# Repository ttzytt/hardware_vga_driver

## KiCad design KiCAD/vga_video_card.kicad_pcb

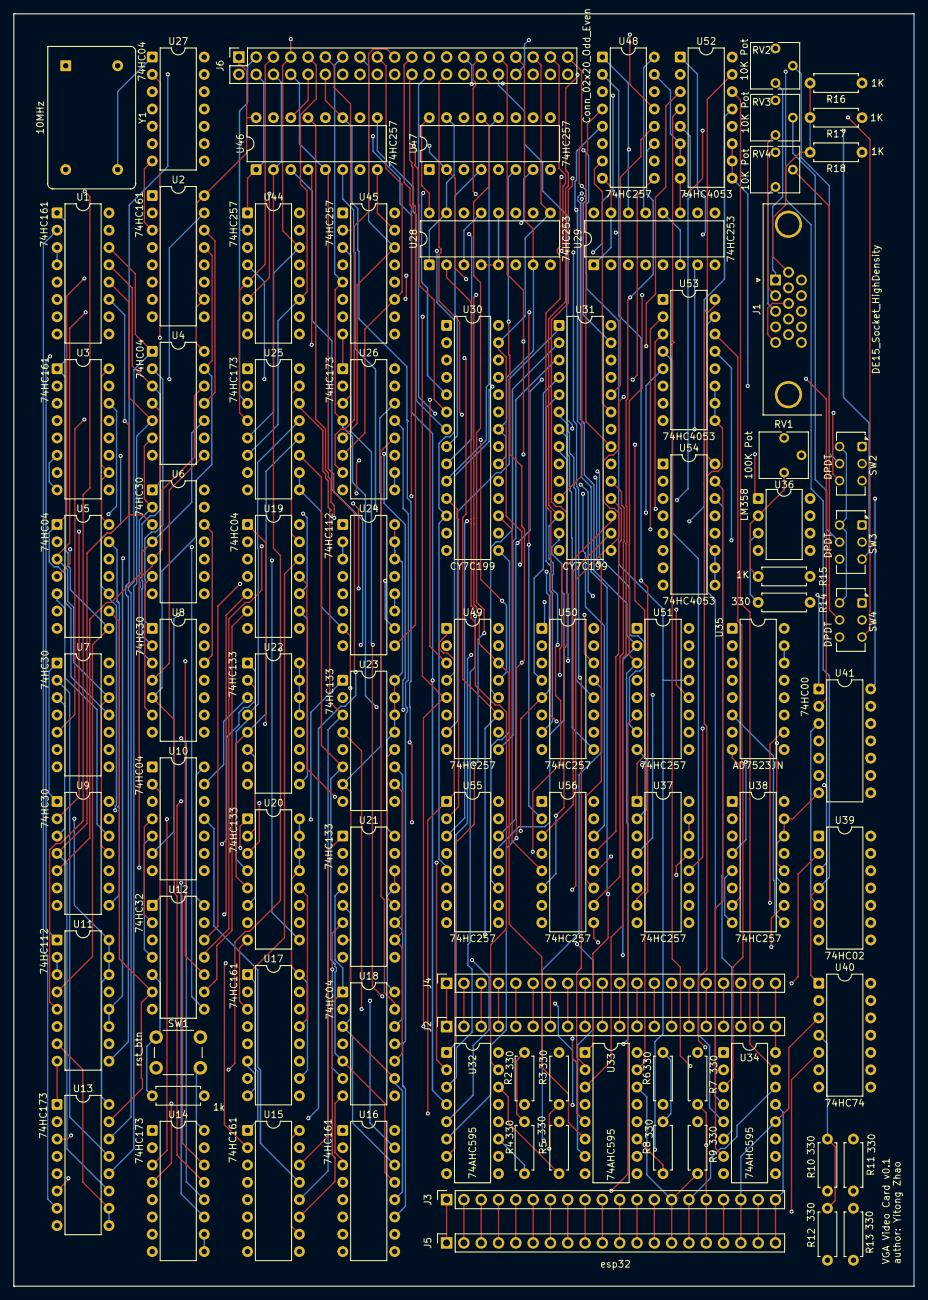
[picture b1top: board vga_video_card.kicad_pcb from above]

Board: 4 copper layers, 132.1 x 186.7 mm, 87 parts (0 on the bottom side), 231 nets.

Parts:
J1: DE15_Socket_HighDensity; DSUB-15-HD_Socket_Horizontal_P2.29x1.90mm_EdgePinOffset3.03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
J2, J3, J4, J5: Conn_01x20; PinSocket_1x20_P2.54mm_Vertical
J6: Conn_02x20_Odd_Even; PinSocket_2x20_P2.54mm_Vertical
R1: 1k; R_Axial_DIN0207_L6.3mm_D2.5mm_P7.62mm_Horizontal
R2, R3, R4, R5, R6, R7, R8, R9, R10, R11, R12, R13, R14: 330; R_Axial_DIN0207_L6.3mm_D2.5mm_P7.62mm_Horizontal
R15, R16, R17, R18: 1K; R_Axial_DIN0207_L6.3mm_D2.5mm_P7.62mm_Horizontal
RV1: 100K Pot; Potentiometer_Vishay_T73YP_Vertical
RV2, RV3, RV4: 10K Pot; Potentiometer_Vishay_T73YP_Vertical
SW1: rst_btn; SW_PUSH_6mm
SW2, SW3, SW4: DPDT; SW_CK_JS202011CQN_DPDT_Straight
U1, U2, U3, U15, U16, U17: 74HC161; DIP-16_W7.62mm
U4, U5, U10, U18, U19, U27: 74HC04; DIP-14_W7.62mm
U6, U7, U8, U9: 74HC30; DIP-14_W7.62mm
U11, U24: 74HC112; DIP-16_W7.62mm
U12: 74HC32; DIP-14_W7.62mm
U13, U14, U25, U26: 74HC173; DIP-16_W7.62mm
U20, U21, U22, U23: 74HC133; DIP-16_W7.62mm
U28, U29: 74HC253; DIP-16_W7.62mm
U30, U31: CY7C199; DIP-28_W7.62mm
U32, U33, U34: 74AHC595; DIP-16_W7.62mm
U35: AD7523JN; DIP-16_W7.62mm
U36: LM358; DIP-8_W7.62mm
U37, U38, U44, U45, U46, U47, U48, U49, U50, U51, U55, U56: 74HC257; DIP-16_W7.62mm
U39: 74HC02; DIP-14_W7.62mm
U40: 74HC74; DIP-14_W7.62mm
U41: 74HC00; DIP-14_W7.62mm
U52, U53, U54: 74HC4053; DIP-16_W7.62mm
Y1: 10MHz; Oscillator_DIP-14

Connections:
+5V: J2.20, J4.20, J6.1, R2.2, R3.2, R4.2, R5.2, R6.2, R7.2, R8.2, R9.2, R10.2, R11.2, R12.2, R13.2, SW1.2, U1.7 (CEP), U1.10 (CET), U1.16 (VCC), U2.7 (CEP), U2.10 (CET), U2.16 (VCC), U3.7 (CEP), U3.10 (CET), U3.16 (VCC), U4.14 (VCC), U5.14 (VCC), U6.14 (VCC), U7.14 (VCC), U8.14 (VCC), U9.14 (VCC), U10.14 (VCC), U11.14 (~R), U11.15 (~R), U11.16 (VCC), U12.14 (VCC), U13.16 (VCC), U14.16 (VCC), U15.7 (CEP), U15.10 (CET), U15.16 (VCC), U16.7 (CEP), U16.10 (CET), U16.16 (VCC), U17.7 (CEP), U17.10 (CET), U17.16 (VCC), U18.14 (VCC), U19.14 (VCC), U20.13, U20.14, U20.15, U20.16 (VCC), U21.13, U21.14, U21.15, U21.16 (VCC), U22.13, U22.14, U22.15, U22.16 (VCC), U23.13, U23.14, U23.15, U23.16 (VCC), U24.14 (~R), U24.15 (~R), U24.16 (VCC), U25.16 (VCC), U26.16 (VCC), U27.14 (VCC), U28.3 (I3a), U28.10 (I0b), U28.11 (I1b), U28.13 (I3b), U28.16 (VCC), U29.6 (I0a), U29.10 (I0b), U29.12 (I2b), U29.13 (I3b), U29.16 (VCC), U30.28 (VCC), U31.28 (VCC), U32.16 (VCC), U33.16 (VCC), U34.16 (VCC), U35.14 (VCC), U35.15 (VREF), U36.8 (V+), U37.16 (VCC), U38.16 (VCC), U39.14 (VCC), U40.2 (D), U40.4 (~S), U40.14 (VCC), U41.14 (VCC), U44.16 (VCC), U45.16 (VCC), U46.16 (VCC), U47.16 (VCC), U48.16 (VCC), U49.16 (VCC), U50.16 (VCC), U51.16 (VCC), U52.16 (VDD), U53.16 (VDD), U54.16 (VDD), U55.16 (VCC), U56.16 (VCC), Y1.1 (EN), Y1.14 (Vcc)
/ADC_module/D0: U35.13 (D0(LSB)), U37.4 (Za)
/ADC_module/D1: U35.12 (D1), U37.7 (Zb)
/ADC_module/D2: U35.11 (D2), U37.12 (Zc)
/ADC_module/D3: U35.10 (D3), U37.9 (Zd)
/ADC_module/D4: U35.9 (D4), U38.4 (Za)
/ADC_module/D5: U35.8 (D5), U38.7 (Zb)
/ADC_module/D6: U35.7 (D6), U38.12 (Zc)
/ADC_module/D7: U35.6 (D7), U38.9 (Zd)
/ADC_module/I0: U37.3 (I1a), U55.4 (Za)
/ADC_module/I1: U37.6 (I1b), U55.7 (Zb)
/ADC_module/I2: U37.13 (I1c), U55.12 (Zc)
/ADC_module/I3: U37.10 (I1d), U55.9 (Zd)
/ADC_module/I4: U38.3 (I1a), U56.4 (Za)
/ADC_module/I5: U38.6 (I1b), U56.7 (Zb)
/ADC_module/I6: U38.13 (I1c), U56.12 (Zc)
/ADC_module/I7: U38.10 (I1d), U56.9 (Zd)
/RAM0_~CE: J6.33, U28.7 (Za), U30.20 (~CE), U30.22 (~OE)
/RAM0_~WE: J6.35, U28.9 (Zb), U30.27 (~WE), U41.1
/RAM1_~CE: J6.37, U29.7 (Za), U31.20 (~CE), U31.22 (~OE)
/RAM1_~WE: J6.39, U29.9 (Zb), U31.27 (~WE), U41.2
/RAM_module/RAM0_a0: U30.21 (A0), U44.4 (Za)
/RAM_module/RAM0_a1: U30.23 (A1), U44.7 (Zb)
/RAM_module/RAM0_a2: U30.24 (A2), U44.12 (Zc)
/RAM_module/RAM0_a3: U30.25 (A3), U44.9 (Zd)
/RAM_module/RAM0_a4: U30.26 (A4), U45.4 (Za)
/RAM_module/RAM0_a5: U30.1 (A5), U45.7 (Zb)
/RAM_module/RAM0_a6: U30.2 (A6), U45.12 (Zc)
/RAM_module/RAM0_a7: U30.3 (A7), U45.9 (Zd)
/RAM_module/RAM0_a8: U30.4 (A8), U46.4 (Za)
/RAM_module/RAM0_a9: U30.5 (A9), U46.7 (Zb)
/RAM_module/RAM0_a10: U30.6 (A10), U46.12 (Zc)
/RAM_module/RAM0_a11: U30.7 (A11), U46.9 (Zd)
/RAM_module/RAM0_a12: U30.8 (A12), U47.4 (Za)
/RAM_module/RAM0_a13: U30.9 (A13), U47.7 (Zb)
/RAM_module/RAM0_a14: U30.10 (A14), U47.12 (Zc)
/RAM_module/RAM0_d0: U30.11 (D0), U52.13 (X1), U55.2 (I0a)
/RAM_module/RAM0_d1: U30.12 (D1), U52.1 (Y1), U55.5 (I0b)
/RAM_module/RAM0_d2: U30.13 (D2), U52.3 (Z1), U55.14 (I0c)
/RAM_module/RAM0_d3: U30.15 (D3), U53.13 (X1), U55.11 (I0d)
/RAM_module/RAM0_d4: U30.16 (D4), U53.1 (Y1), U56.2 (I0a)
/RAM_module/RAM0_d5: U30.17 (D5), U53.3 (Z1), U56.5 (I0b)
/RAM_module/RAM0_d6: U30.18 (D6), U54.13 (X1), U56.14 (I0c)
/RAM_module/RAM0_d7: U30.19 (D7), U54.1 (Y1), U56.11 (I0d)
/RAM_module/RAM1_a0: U31.21 (A0), U48.4 (Za)
/RAM_module/RAM1_a1: U31.23 (A1), U48.7 (Zb)
/RAM_module/RAM1_a2: U31.24 (A2), U48.12 (Zc)
/RAM_module/RAM1_a3: U31.25 (A3), U48.9 (Zd)
/RAM_module/RAM1_a4: U31.26 (A4), U49.4 (Za)
/RAM_module/RAM1_a5: U31.1 (A5), U49.7 (Zb)
/RAM_module/RAM1_a6: U31.2 (A6), U49.12 (Zc)
/RAM_module/RAM1_a7: U31.3 (A7), U49.9 (Zd)
/RAM_module/RAM1_a8: U31.4 (A8), U50.4 (Za)
/RAM_module/RAM1_a9: U31.5 (A9), U50.7 (Zb)
/RAM_module/RAM1_a10: U31.6 (A10), U50.12 (Zc)
/RAM_module/RAM1_a11: U31.7 (A11), U50.9 (Zd)
/RAM_module/RAM1_a12: U31.8 (A12), U51.4 (Za)
/RAM_module/RAM1_a13: U31.9 (A13), U51.7 (Zb)
/RAM_module/RAM1_a14: U31.10 (A14), U51.12 (Zc)
/RAM_module/RAM1_d0: U31.11 (D0), U52.12 (X0), U55.3 (I1a)
/RAM_module/RAM1_d1: U31.12 (D1), U52.2 (Y0), U55.6 (I1b)
/RAM_module/RAM1_d2: U31.13 (D2), U52.5 (Z0), U55.13 (I1c)
/RAM_module/RAM1_d3: U31.15 (D3), U53.12 (X0), U55.10 (I1d)
/RAM_module/RAM1_d4: U31.16 (D4), U53.2 (Y0), U56.3 (I1a)
/RAM_module/RAM1_d5: U31.17 (D5), U53.5 (Z0), U56.6 (I1b)
/RAM_module/RAM1_d6: U31.18 (D6), U54.12 (X0), U56.13 (I1c)
/RAM_module/RAM1_d7: U31.19 (D7), U54.2 (Y0), U56.10 (I1d)
/RAM_module/RAM_bus_mux/w_addr0: U33.15 (QA), U44.3 (I1a), U48.2 (I0a)
/RAM_module/RAM_bus_mux/w_addr1: U33.1 (QB), U44.6 (I1b), U48.5 (I0b)
/RAM_module/RAM_bus_mux/w_addr2: U33.2 (QC), U44.13 (I1c), U48.14 (I0c)
/RAM_module/RAM_bus_mux/w_addr3: U33.3 (QD), U44.10 (I1d), U48.11 (I0d)
/RAM_module/RAM_bus_mux/w_addr4: U33.4 (QE), U45.3 (I1a), U49.2 (I0a)
/RAM_module/RAM_bus_mux/w_addr5: U33.5 (QF), U45.6 (I1b), U49.5 (I0b)
/RAM_module/RAM_bus_mux/w_addr6: U33.6 (QG), U45.13 (I1c), U49.14 (I0c)
/RAM_module/RAM_bus_mux/w_addr7: U33.7 (QH), U45.10 (I1d), U49.11 (I0d)
/RAM_module/RAM_bus_mux/w_addr8: U32.1 (QB), U46.3 (I1a), U50.2 (I0a)
/RAM_module/RAM_bus_mux/w_addr9: U32.2 (QC), U46.6 (I1b), U50.5 (I0b)
/RAM_module/RAM_bus_mux/w_addr10: U32.3 (QD), U46.13 (I1c), U50.14 (I0c)
/RAM_module/RAM_bus_mux/w_addr11: U32.4 (QE), U46.10 (I1d), U50.11 (I0d)
/RAM_module/RAM_bus_mux/w_addr12: U32.5 (QF), U47.3 (I1a), U51.2 (I0a)
/RAM_module/RAM_bus_mux/w_addr13: U32.6 (QG), U47.6 (I1b), U51.5 (I0b)
/RAM_module/RAM_bus_mux/w_addr14: U32.7 (QH), U47.13 (I1c), U51.14 (I0c)
/RAM_module/RAM_bus_mux/w_data0: U34.15 (QA), U52.14 (X)
/RAM_module/RAM_bus_mux/w_data1: U34.1 (QB), U52.15 (Y)
/RAM_module/RAM_bus_mux/w_data2: U34.2 (QC), U52.4 (Z)
/RAM_module/RAM_bus_mux/w_data3: U34.3 (QD), U53.14 (X)
/RAM_module/RAM_bus_mux/w_data4: U34.4 (QE), U53.15 (Y)
/RAM_module/RAM_bus_mux/w_data5: U34.5 (QF), U53.4 (Z)
/RAM_module/RAM_bus_mux/w_data6: U34.6 (QG), U54.14 (X)
/RAM_module/RAM_bus_mux/w_data7: U34.7 (QH), U54.15 (Y)
/RAM_module/RAM_bus_mux/w_j_addr0: U28.2 (A1), U29.2 (A1), U32.15 (QA)
/RAM_module/await_upd: J3.1, J5.1, U40.5 (Q)
/RAM_module/ext_graphics_rclk: J3.18, J5.18, R2.1, R6.1, R10.1, U32.12 (RCLK), U33.12 (RCLK), U34.12 (RCLK), U40.3 (C)
/RAM_module/ext_graphics_source/data_ser: J3.15, J5.15, R13.1, U34.14 (SER)
/RAM_module/ext_graphics_source/data_srclk: J3.17, J5.17, R4.1, R8.1, R12.1, U32.11 (SRCLK), U33.11 (SRCLK), U34.11 (SRCLK)
/RAM_module/ext_graphics_source/data_~srclr: J3.16, J5.16, R3.1, R7.1, R11.1, U32.10 (~SRCLR), U33.10 (~SRCLR), U34.10 (~SRCLR)
/RAM_module/ext_graphics_source/i_addr_ser: J3.14, J5.14, R9.1, U33.14 (SER)
/RAM_module/ext_graphics_source/j_addr_ser: J3.13, J5.13, R5.1, U32.14 (SER)
/RAM_module/r_i_addr0: J6.3, U25.3 (Q0), U44.2 (I0a), U48.3 (I1a)
/RAM_module/r_i_addr1: J6.5, U25.4 (Q1), U44.5 (I0b), U48.6 (I1b)
/RAM_module/r_i_addr2: J6.7, U25.5 (Q2), U44.14 (I0c), U48.13 (I1c)
/RAM_module/r_i_addr3: J6.9, U25.6 (Q3), U44.11 (I0d), U48.10 (I1d)
/RAM_module/r_i_addr4: J6.11, U26.3 (Q0), U45.2 (I0a), U49.3 (I1a)
/RAM_module/r_i_addr5: J6.13, U26.4 (Q1), U45.5 (I0b), U49.6 (I1b)
/RAM_module/r_i_addr6: J6.15, U26.5 (Q2), U45.14 (I0c), U49.13 (I1c)
/RAM_module/r_i_addr7: J6.17, U26.6 (Q3), U45.11 (I0d), U49.10 (I1d)
/RAM_module/r_j_addr0: J6.4, U13.3 (Q0), U28.14 (A0), U29.14 (A0), U44.1 (S), U45.1 (S), U46.1 (S), U47.1 (S), U48.1 (S), U49.1 (S), U50.1 (S), U51.1 (S), U52.9 (C), U52.10 (B), U52.11 (A), U53.9 (C), U53.10 (B), U53.11 (A), U54.9 (C), U54.10 (B), U54.11 (A), U55.1 (S), U56.1 (S)
/RAM_module/r_j_addr1: J6.6, U13.4 (Q1), U46.2 (I0a), U50.3 (I1a)
/RAM_module/r_j_addr2: J6.8, U13.5 (Q2), U46.5 (I0b), U50.6 (I1b)
/RAM_module/r_j_addr3: J6.10, U13.6 (Q3), U46.14 (I0c), U50.13 (I1c)
/RAM_module/r_j_addr4: J6.12, U14.3 (Q0), U46.11 (I0d), U50.10 (I1d)
/RAM_module/r_j_addr5: J6.14, U14.4 (Q1), U47.2 (I0a), U51.3 (I1a)
/RAM_module/r_j_addr6: J6.16, U14.5 (Q2), U47.5 (I0b), U51.6 (I1b)
/RAM_module/r_j_addr7: J6.18, U14.6 (Q3), U47.14 (I0c), U51.13 (I1c)
/VGA_B: J1.3, J6.27, R18.1, RV4.1
/VGA_G: J1.2, J6.25, R17.1, RV3.1
/VGA_R: J1.1, J6.23, R16.1, RV2.1
/eo_frame: J6.21, U12.12, U19.10
/eo_line: J6.19, U5.10, U10.5, U12.4, U15.2 (CP), U25.7 (Cp), U26.7 (Cp)
/ext_B: J6.30, SW4.3 (C), SW4.4 (A)
/ext_G: J6.28, SW3.3 (C), SW3.4 (A)
/ext_R: J6.26, SW2.3 (C), SW2.4 (A)
/h_sync: J1.13, J6.29, U11.5 (Q)
/horizontal_counter/CLK: U1.2 (CP), U13.7 (Cp), U14.7 (Cp), U27.1, Y1.8 (OUT)
/horizontal_counter/bit_0: U1.14 (Q0), U4.1, U13.14 (D0)
/horizontal_counter/bit_1: U1.13 (Q1), U4.3, U7.2, U8.2, U13.13 (D1)
/horizontal_counter/bit_2: U1.12 (Q2), U4.5, U13.12 (D2)
/horizontal_counter/bit_3: U1.11 (Q3), U4.9, U6.3, U9.4, U13.11 (D3)
/horizontal_counter/bit_4: U2.14 (Q0), U4.11, U7.5, U14.14 (D0)
/horizontal_counter/bit_5: U2.13 (Q1), U4.13, U7.6, U8.5, U14.13 (D1)
/horizontal_counter/bit_6: U2.12 (Q2), U5.1, U7.11, U14.12 (D2)
/horizontal_counter/bit_7: U2.11 (Q3), U5.3, U7.12, U8.11, U9.11, U14.11 (D3)
/horizontal_counter/bit_8: U3.14 (Q0), U5.5, U6.12, U8.12, U9.12
/horizontal_counter/eo_fporch_210: U10.2, U12.1
/horizontal_counter/eo_syncp_242: U10.4, U12.2
/horizontal_counter/eo_vis_200: U5.12, U11.11 (J), U11.12 (K)
/horizontal_counter/rst: U5.9, U12.6, U13.15 (Mr), U14.15 (Mr)
/horizontal_counter/~CLK: U11.1 (C), U11.13 (C), U27.2
/horizontal_counter/~bit_0: U4.2, U7.1, U8.1, U9.1
/horizontal_counter/~bit_1: U4.4, U6.1, U9.2
/horizontal_counter/~bit_2: U4.6, U6.2, U7.3, U8.3, U9.3
/horizontal_counter/~bit_3: U4.8, U7.4, U8.4
/horizontal_counter/~bit_4: U4.10, U6.4, U9.5
/horizontal_counter/~bit_5: U4.12, U6.5, U9.6
/horizontal_counter/~bit_6: U5.2, U6.6, U8.6
/horizontal_counter/~bit_7: U5.4, U6.11
/horizontal_counter/~eo_line: U10.6, U24.1 (C), U24.13 (C)
/horizontal_counter/~is_h_vis_area: U11.7 (~Q), U13.9 (E1), U13.10 (E2), U14.9 (E1), U14.10 (E2), U39.2
/horizontal_counter/~rst: U1.1 (~MR), U2.1 (~MR), U3.1 (~MR), U5.8, U11.4 (~S), U11.10 (~S)
/int_brightness: J6.32, RV1.2, SW2.1 (A), SW2.6 (C), SW3.1 (A), SW3.6 (C), SW4.1 (A), SW4.6 (C), U36.1
/is_h_vis_area: J6.20, U11.9 (Q)
/is_v_vis_area: J6.22, U24.9 (Q)
/is_vis_area: J6.24, U37.1 (S), U38.1 (S), U39.1
/mrst: R1.2, SW1.1, U12.5, U12.13, U39.6
/v_sync: J1.14, J6.31, U24.5 (Q)
/vertical_counter/bit_0: U10.9, U15.14 (Q0), U21.1, U22.1
/vertical_counter/bit_1: U10.11, U15.13 (Q1)
/vertical_counter/bit_2: U10.13, U15.12 (Q2), U22.3, U23.3, U25.14 (D0)
/vertical_counter/bit_3: U15.11 (Q3), U18.1, U20.4, U21.4, U22.4, U25.13 (D1)
/vertical_counter/bit_4: U16.14 (Q0), U18.3, U20.5, U21.5, U22.5, U23.5, U25.12 (D2)
/vertical_counter/bit_5: U16.13 (Q1), U18.5, U23.6, U25.11 (D3)
/vertical_counter/bit_6: U16.12 (Q2), U18.9, U20.7, U21.7, U22.7, U23.7, U26.14 (D0)
/vertical_counter/bit_7: U16.11 (Q3), U18.11, U26.13 (D1)
/vertical_counter/bit_8: U17.14 (Q0), U18.13, U26.12 (D2)
/vertical_counter/bit_9: U17.13 (Q1), U19.1, U20.12, U21.12, U22.12, U23.12, U26.11 (D3)
/vertical_counter/eo_fporch_601: U12.9, U19.6
/vertical_counter/eo_syncp_605: U12.10, U19.8
/vertical_counter/eo_vis_600: U19.4, U24.11 (J), U24.12 (K)
/vertical_counter/rst: U12.11, U19.13, U25.15 (Mr), U26.15 (Mr)
/vertical_counter/~bit_0: U10.8, U20.1, U23.1
/vertical_counter/~bit_1: U10.10, U20.2, U21.2, U22.2, U23.2
/vertical_counter/~bit_2: U10.12, U20.3, U21.3
/vertical_counter/~bit_3: U18.2, U23.4
/vertical_counter/~bit_5: U18.6, U20.6, U21.6, U22.6
/vertical_counter/~bit_7: U18.10, U20.10, U21.10, U22.10, U23.10
/vertical_counter/~bit_8: U18.12, U20.11, U21.11, U22.11, U23.11
/vertical_counter/~is_v_vis_area: U24.7 (~Q), U25.9 (E1), U25.10 (E2), U26.9 (E1), U26.10 (E2), U39.3
/vertical_counter/~rst: U15.1 (~MR), U16.1 (~MR), U17.1 (~MR), U19.12, U24.4 (~S), U24.10 (~S)
/writing_RAM: J6.34, U39.4, U40.1 (~R)
GND: J1.5, J1.6, J1.7, J1.8, J1.10, J3.20, J5.20, J6.2, R1.1, R14.2, R15.2, R16.2, R17.2, R18.2, U1.3 (D0), U1.4 (D1), U1.5 (D2), U1.6 (D3), U1.8 (GND), U1.9 (~PE), U2.3 (D0), U2.4 (D1), U2.5 (D2), U2.6 (D3), U2.8 (GND), U2.9 (~PE), U3.3 (D0), U3.4 (D1), U3.5 (D2), U3.6 (D3), U3.8 (GND), U3.9 (~PE), U4.7 (GND), U5.7 (GND), U6.7 (GND), U7.7 (GND), U8.7 (GND), U9.7 (GND), U10.7 (GND), U11.8 (GND), U12.7 (GND), U13.1 (Oe1), U13.2 (Oe2), U13.8 (GND), U14.1 (Oe1), U14.2 (Oe2), U14.8 (GND), U15.3 (D0), U15.4 (D1), U15.5 (D2), U15.6 (D3), U15.8 (GND), U15.9 (~PE), U16.3 (D0), U16.4 (D1), U16.5 (D2), U16.6 (D3), U16.8 (GND), U16.9 (~PE), U17.3 (D0), U17.4 (D1), U17.5 (D2), U17.6 (D3), U17.8 (GND), U17.9 (~PE), U18.7 (GND), U19.7 (GND), U20.8 (GND), U21.8 (GND), U22.8 (GND), U23.8 (GND), U24.8 (GND), U25.1 (Oe1), U25.2 (Oe2), U25.8 (GND), U26.1 (Oe1), U26.2 (Oe2), U26.8 (GND), U27.7 (GND), U28.1 (OEa), U28.4 (I2a), U28.5 (I1a), U28.6 (I0a), U28.8 (GND), U28.12 (I2b), U28.15 (OEb), U29.1 (OEa), U29.3 (I3a), U29.4 (I2a), U29.5 (I1a), U29.8 (GND), U29.11 (I1b), U29.15 (OEb), U30.14 (GND), U31.14 (GND), U32.8 (GND), U32.13 (~OE), U33.8 (GND), U33.13 (~OE), U34.8 (GND), U34.13 (~OE), U35.2 (I_OUT2), U35.3 (GND), U36.4 (V-), U37.2 (I0a), U37.5 (I0b), U37.8 (GND), U37.11 (I0d), U37.14 (I0c), U37.15 (OE), U38.2 (I0a), U38.5 (I0b), U38.8 (GND), U38.11 (I0d), U38.14 (I0c), U38.15 (OE), U39.7 (GND), U40.7 (GND), U41.7 (GND), U44.8 (GND), U44.15 (OE), U45.8 (GND), U45.15 (OE), U46.8 (GND), U46.15 (OE), U47.8 (GND), U47.15 (OE), U48.8 (GND), U48.15 (OE), U49.8 (GND), U49.15 (OE), U50.8 (GND), U50.15 (OE), U51.8 (GND), U51.15 (OE), U52.6 (Inh), U52.7 (VEE), U52.8 (VSS), U53.6 (Inh), U53.7 (VEE), U53.8 (VSS), U54.6 (Inh), U54.7 (VEE), U54.8 (VSS), U55.8 (GND), U55.15 (OE), U56.8 (GND), U56.15 (OE), Y1.7 (GND)
unnamed: J2.1, J4.1
unnamed: J2.2, J4.2
unnamed: J2.3, J4.3
unnamed: J2.4, J4.4
unnamed: J2.5, J4.5
unnamed: J2.6, J4.6
unnamed: J2.7, J4.7
unnamed: J2.8, J4.8
unnamed: J2.9, J4.9
unnamed: J2.10, J4.10
unnamed: J2.11, J4.11
unnamed: J2.12, J4.12
unnamed: J2.13, J4.13
unnamed: J2.14, J4.14
unnamed: J2.15, J4.15
unnamed: J2.16, J4.16
unnamed: J2.17, J4.17
unnamed: J2.18, J4.18
unnamed: J2.19, J4.19
unnamed: J3.2, J5.2
unnamed: J3.3, J5.3
unnamed: J3.4, J5.4
unnamed: J3.5, J5.5
unnamed: J3.6, J5.6
unnamed: J3.7, J5.7
unnamed: J3.8, J5.8
unnamed: J3.9, J5.9
unnamed: J3.10, J5.10
unnamed: J3.11, J5.11
unnamed: J3.12, J5.12
unnamed: J3.19, J5.19
unnamed: RV2.2, SW2.2 (B), SW2.5 (B)
unnamed: RV3.2, SW3.2 (B), SW3.5 (B)
unnamed: RV4.2, SW4.2 (B), SW4.5 (B)
unnamed: U1.15 (TC), U2.2 (CP)
unnamed: U2.15 (TC), U3.2 (CP)
unnamed: U5.11, U6.8
unnamed: U5.13, U9.8
unnamed: U8.8, U10.1
unnamed: U7.8, U10.3
unnamed: U11.2 (K), U11.3 (J), U12.3
unnamed: U15.15 (TC), U16.2 (CP)
unnamed: U16.15 (TC), U17.2 (CP)
unnamed: U19.3, U20.9
unnamed: U19.5, U21.9
unnamed: U19.9, U22.9
unnamed: U19.11, U23.9
unnamed: U12.8, U24.2 (K), U24.3 (J)
unnamed: R14.1, U35.1 (I_OUT1), U36.3 (+)
unnamed: R15.1, RV1.1, U36.2 (-)
unnamed: U39.5, U41.3

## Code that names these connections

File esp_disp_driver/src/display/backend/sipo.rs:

use crate::sipo::*;
use crate::display::pix_writer::PixelWriter;
use esp_hal::{gpio::AnyPin, peripherals}; 

pub struct BwPixelWriter8h8v1ch8<'a> {
    // 8 bit for H address, 8 bit for V address
    // 1ch8: 1 channel, 8 bit color depth (BW)
    pub p_sipo_bank : ParallelBank<'a, 3, 1>,
}

pub struct VgaHwResources<'a>{ 
    pub rclk : AnyPin<'a>, 
    pub srclk : AnyPin<'a>, 
    pub srclr_al : AnyPin<'a>,
    pub data_ser : AnyPin<'a>,
    pub i_addr_ser : AnyPin<'a>,
    pub j_addr_ser : AnyPin<'a>,

}

impl BwPixelWriter8h8v1ch8<'_> {
    pub fn from_resources<'a>(res : VgaHwResources<'a>) -> BwPixelWriter8h8v1ch8<'a>{
        let control_pin_cfg = ControlPinCfg {
            srclk : res.srclk,
            rclk : Some(res.rclk),    
            srclr : Some(res.srclr_al),
            clr_active_low : true,
        };
        let control_group = ControlGroup::from_cfg(control_pin_cfg);
        let data_lane = SerLane::from_pin(res.data_ser);
        let i_addr_lane = SerLane::from_pin(res.i_addr_ser);
        let j_addr_lane = SerLane::from_pin(res.j_addr_ser);
        let p_sipo_bank = ParallelBank::new(
            [data_lane, i_addr_lane, j_addr_lane],
            control_group,
        );
        BwPixelWriter8h8v1ch8{
            p_sipo_bank
        }
    }
}

impl<'a> PixelWriter<u8, u8> for BwPixelWriter8h8v1ch8<'a> {
    fn write_pixel(&mut self, i: u8, j: u8, color: u8) {
        let frame = [
            [color], // BW channel
            [i],    // V address
            [j],    // H address
        ];
        self.p_sipo_bank.write_exact(frame);
    }

    #[inline(always)]
    fn addr_range(&self) -> ((u8, u8), (u8, u8)) {
        ((0, 150), (0, 200))
    }

    #[inline(always)]
    fn color_range(&self) -> (u8, u8) {
        (0, 255)
    }
}

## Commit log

2025-09-24 init commit
2025-09-24 add file
2025-10-01 finished SRAM_controller and changed some naming
2025-10-03 impl bus_mux and SRAM_controller
2025-10-03 impl SRAM_module
2025-11-12 started driver code
2025-11-15 switched to probe-rs and JTAG as the flashing problem has been fixed
2025-11-19 completed sipo.rs and pixel writers
2025-11-22 finished schematics for hcounter, working on vcounter; rust code need to be cleaned up
2025-11-24 assigned footprints
2025-11-26 finished most of the schematics of submodules except DAC, need to work on integration
2025-11-27 finished schematics and footprint assignments; need to figure out +5v connection issue
2025-11-27 fix footprint
2025-11-27 modified debug connector; changed board type in pcb editor
2025-11-27 update pcb
2025-11-27 fix multiple ERCs that made RAM addrs not connecting
2025-11-27 resolve ERCs for addr combiner
2025-11-27 clean up; resolve ERC warnings
2025-11-27 resolved most ERC errors
2025-11-27 resolved all ERC errors, kicad got some stupid bugs
2025-11-28 partially finished pcb layout
2025-11-28 finished layout
2025-11-28 finished layout and silkscreen
2025-11-28 resolve DRC warnings
2025-11-28 generate gerber file
2025-11-28 add grill file
2025-12-02 refactored sipo.rs, need to refactor other related parts as well
2025-12-02 add constructor for clearline and latchline
2025-12-02 add pix_writer; clean up, able to compile now
2025-12-03 impl drawer
2025-12-03 add pure color demo
2025-12-05 correct order of frame in PixelWriter::write_pixel
2025-12-06 add par_data_reader
2025-12-06 added par data reader
2025-12-07 finish bus_dec_demo
2025-12-15 updated KiCAD todos
2025-12-15 fixed the numbers of horizontal counter NAND gates
2025-12-15 schematics disabled PE
2025-12-17 add files
2025-12-17 add schematics todos for DAC and RAM state controller
2025-12-23 update DAC schematics; update pin layout for esp32 connector; update RAM state controller input pin
2025-12-24 passed DRC for PCB
2025-12-25 fix ic orientation PCB
2025-12-25 fix another ic's orientation, pass DRC
2025-12-25 refine silkscreen
2025-12-25 add fabrication files
